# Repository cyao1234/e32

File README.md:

# ESP32-s2 development board

With drunk components!

---

This is a single board esp32-s2 development board. with two neopixels and an on-board antenna.

It has drunk component placement and some nice freeform traces

The 2.54mm pitch can be fitten in breadboard and used nicely with jumpers

The programming can be done over USB-C ports

---

The scehmatic is easy and simple, giving people the maximum leverage.

Everything is impedance matched, giving the best EMC and high-speed SI performance

---

For bom see `bom.csv`

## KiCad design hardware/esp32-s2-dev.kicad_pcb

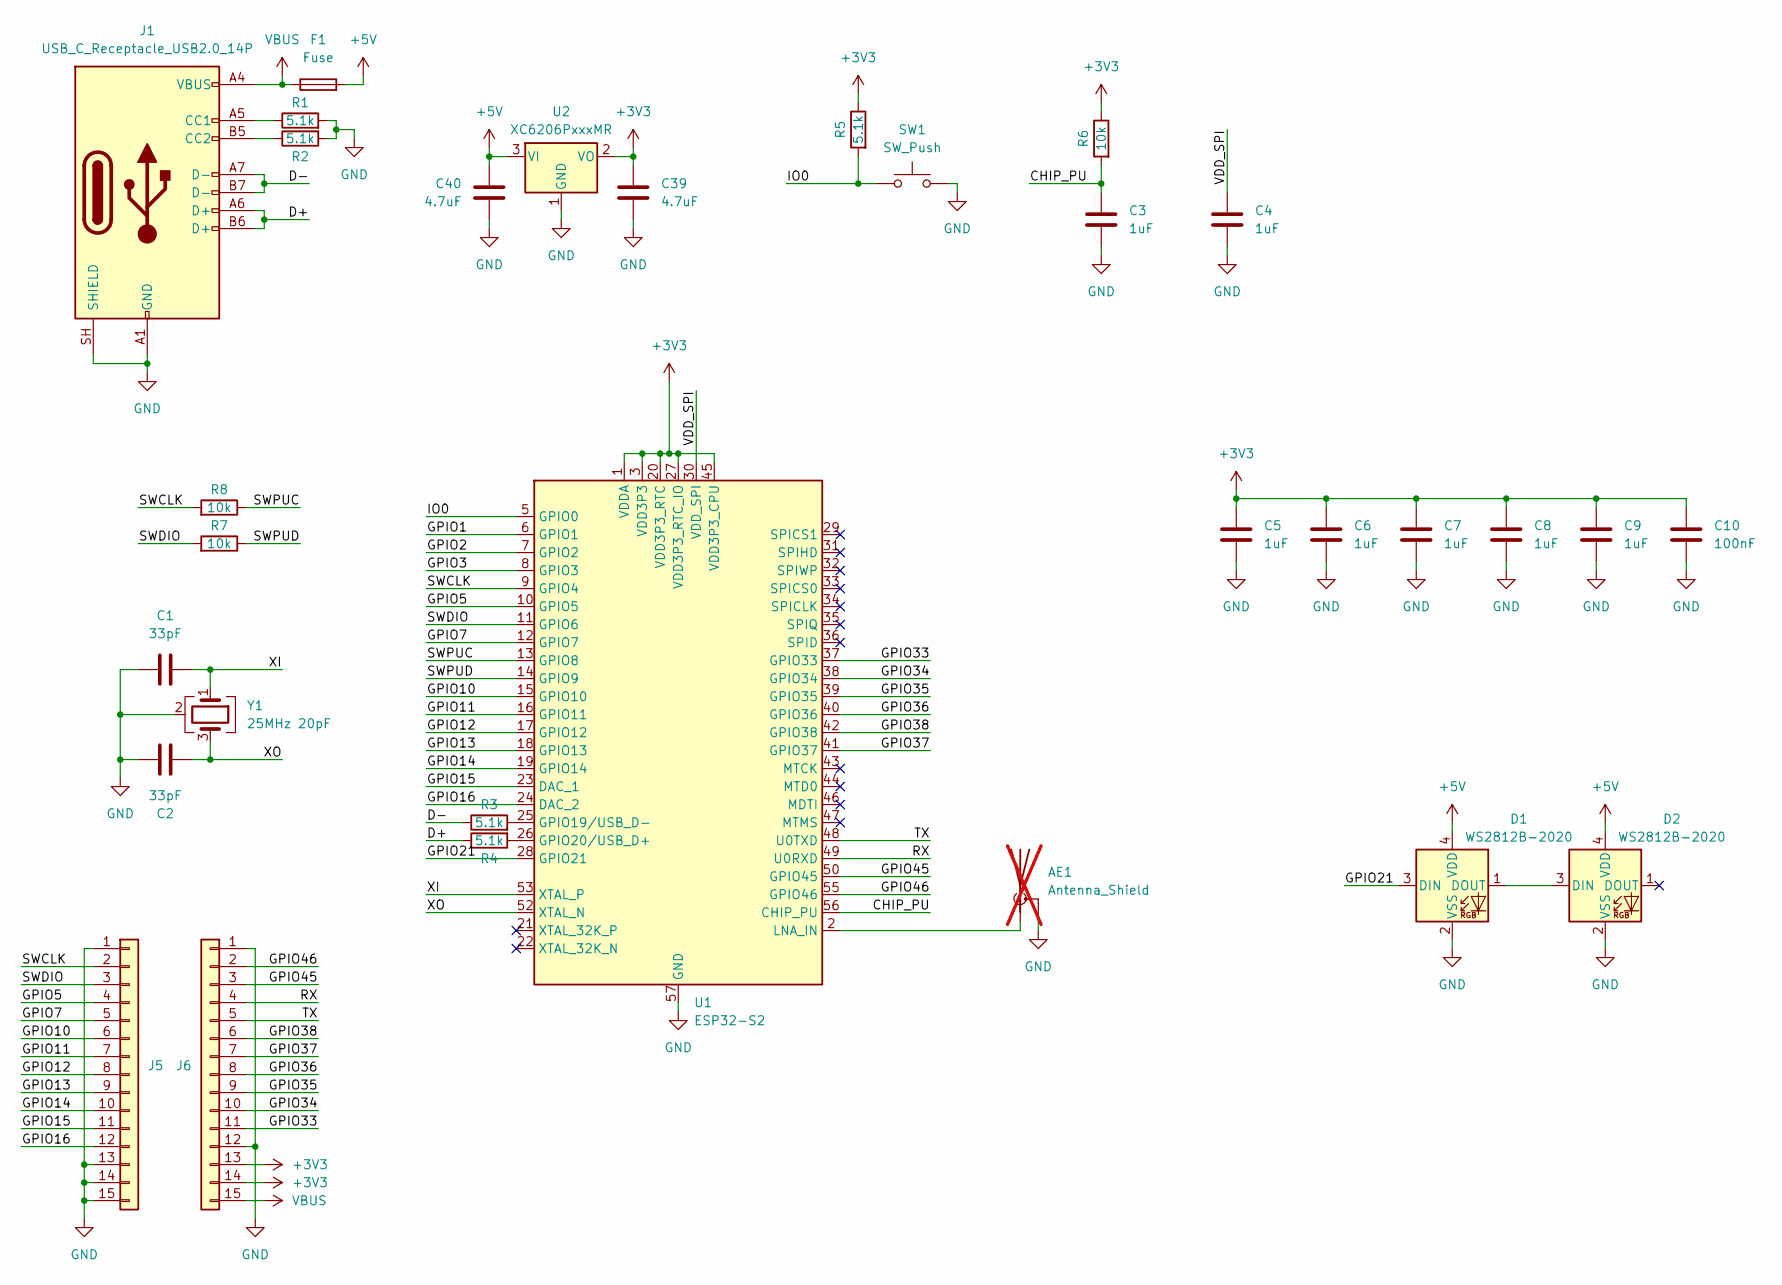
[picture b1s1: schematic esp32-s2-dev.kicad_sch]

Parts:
AE1: Antenna_Shield; Texas_SWRA117D_2.4GHz_Left; not fitted
C1, C2: 33pF; C_0402_1005Metric; LCSC Part # C5137486
C3, C4, C5, C6, C7, C8, C9: 1uF; C_0402_1005Metric; LCSC Part # C52923
C10: 100nF; C_0402_1005Metric; LCSC Part # C1525
C39, C40: 4.7uF; C_0402_1005Metric; LCSC Part # C23733
D1, D2: WS2812B-2020; LED_WS2812B-2020_PLCC4_2.0x2.0mm; LCSC Part # C5349955
F1: Fuse; Fuse_0805_2012Metric
J1: USB_C_Receptacle_USB2.0_14P; USB_C_Receptacle_HRO_TYPE-C-31-M-12; LCSC Part # C165948
J5, J6: Conn_01x15; PinHeader_1x15_P2.54mm_Vertical
R1, R2, R3, R4, R5: 5.1k; R_0402_1005Metric; LCSC Part # C25905
R6, R7, R8: 10k; R_0402_1005Metric; LCSC Part # C25744
SW1: SW_Push; switch_button_TS-1088-AR02016; LCSC Part # C720477
U1: ESP32-S2; QFN-56-1EP_7x7mm_P0.4mm_EP4x4mm_ThermalVias; LCSC Part # C2840995
U2: XC6206PxxxMR; SOT-23-3; LCSC Part # C5446
Y1: 25MHz 20pF; Crystal_SMD_2016-4Pin_2.0x1.6mm; LCSC Part # C37635326

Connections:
+3V3: C5.1, C6.1, C7.1, C8.1, C9.1, C10.1, C39.1, J6.13, J6.14, R5.1, R6.1, U1.1 (VDDA), U1.3 (VDD3P3), U1.4 (VDD3P3), U1.20 (VDD3P3_RTC), U1.27 (VDD3P3_RTC_IO), U1.45 (VDD3P3_CPU), U1.51 (VDDA), U1.54 (VDDA), U2.2 (VO)
+5V: C40.1, D1.4 (VDD), D2.4 (VDD), F1.2, U2.3 (VI)
/CHIP_PU: C3.1, R6.2, U1.56 (CHIP_PU)
/D+: J1.A6 (D+), J1.B6 (D+), R4.1
/D-: J1.A7 (D-), J1.B7 (D-), R3.1
/GPIO1: U1.6 (GPIO1)
/GPIO2: U1.7 (GPIO2)
/GPIO3: U1.8 (GPIO3)
/GPIO5: J5.4, U1.10 (GPIO5)
/GPIO7: J5.5, U1.12 (GPIO7)
/GPIO10: J5.6, U1.15 (GPIO10)
/GPIO11: J5.7, U1.16 (GPIO11)
/GPIO12: J5.8, U1.17 (GPIO12)
/GPIO13: J5.9, U1.18 (GPIO13)
/GPIO14: J5.10, U1.19 (GPIO14)
/GPIO15: J5.11, U1.23 (DAC_1)
/GPIO16: J5.12, U1.24 (DAC_2)
/GPIO21: D1.3 (DIN), U1.28 (GPIO21)
/GPIO33: J6.11, U1.37 (GPIO33)
/GPIO34: J6.10, U1.38 (GPIO34)
/GPIO35: J6.9, U1.39 (GPIO35)
/GPIO36: J6.8, U1.40 (GPIO36)
/GPIO37: J6.7, U1.41 (GPIO37)
/GPIO38: J6.6, U1.42 (GPIO38)
/GPIO45: J6.3, U1.50 (GPIO45)
/GPIO46: J6.2, U1.55 (GPIO46)
/IO0: R5.2, SW1.1, U1.5 (GPIO0)
/RX: J6.4, U1.49 (U0RXD)
/SWCLK: J5.2, R8.2, U1.9 (GPIO4)
/SWDIO: J5.3, R7.2, U1.11 (GPIO6)
/SWPUC: R8.1, U1.13 (GPIO8)
/SWPUD: R7.1, U1.14 (GPIO9)
/TX: J6.5, U1.48 (U0TXD)
/VDD_SPI: C4.1, U1.30 (VDD_SPI)
/XI: C1.2, U1.53 (XTAL_P), Y1.1
/XO: C2.2, U1.52 (XTAL_N), Y1.3
GND: AE1.2 (Shield), C1.1, C2.1, C3.2, C4.2, C5.2, C6.2, C7.2, C8.2, C9.2, C10.2, C39.2, C40.2, D1.2 (VSS), D2.2 (VSS), J1.A1 (GND), J1.A12 (GND), J1.B1 (GND), J1.B12 (GND), J1.SH (SHIELD), J5.1, J5.13, J5.14, J5.15, J6.1, J6.12, R1.2, R2.2, SW1.2, U1.57 (GND), U2.1 (GND), Y1.2 (G), Y1.4 (G)
unnamed: AE1.1 (A), U1.2 (LNA_IN)
unnamed: D1.1 (DOUT), D2.3 (DIN)
unnamed: J1.A5 (CC1), R1.1
unnamed: J1.B5 (CC2), R2.1
unnamed: R3.2, U1.25 (GPIO19/USB_D-)
unnamed: R4.2, U1.26 (GPIO20/USB_D+)
VBUS: F1.1, J1.A4 (VBUS), J1.A9 (VBUS), J1.B4 (VBUS), J1.B9 (VBUS), J6.15

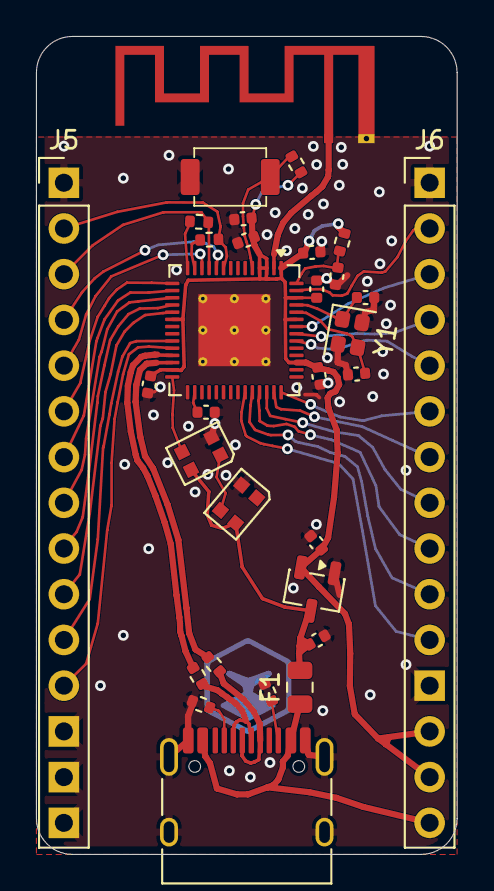
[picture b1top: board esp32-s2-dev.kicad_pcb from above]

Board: 2 copper layers, 23.4 x 45.4 mm, 32 parts (1 on the bottom side), 41 nets.

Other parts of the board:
H2: MountingHole; Icy Electronics Logo

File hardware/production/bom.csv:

Designator,Footprint,Quantity,Value,LCSC Part #
"C1, C2",0402,2,33pF,C5137486
C10,0402,1,100nF,C1525
"C3, C4, C5, C6, C7, C8, C9",0402,7,1uF,C52923
"C39, C40",0402,2,4.7uF,C23733
"D1, D2",LED_WS2812B-2020_PLCC4_2.0x2.0mm,2,WS2812B-2020,C5349955
F1,0805,1,Fuse,
J1,USB_C_Receptacle_HRO_TYPE-C-31-M-12,1,USB_C_Receptacle_USB2.0_14P,C165948
"J5, J6",PinHeader_1x15_P2.54mm_Vertical,2,Conn_01x15,
"R1, R2, R3, R4, R5",0402,5,5.1k,C25905
"R6, R7, R8",0402,3,10k,C25744
SW1,switch_button_TS-1088-AR02016,1,SW_Push,C720477
U1,QFN-56-1EP_7x7mm_P0.4mm_EP4x4mm_ThermalVias,1,ESP32-S2,C2840995
U2,SOT-23-3,1,XC6206PxxxMR,C5446
Y1,Crystal_SMD_2016-4Pin_2.0x1.6mm,1,25MHz 20pF,C37635326

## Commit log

2026-06-07 Push
